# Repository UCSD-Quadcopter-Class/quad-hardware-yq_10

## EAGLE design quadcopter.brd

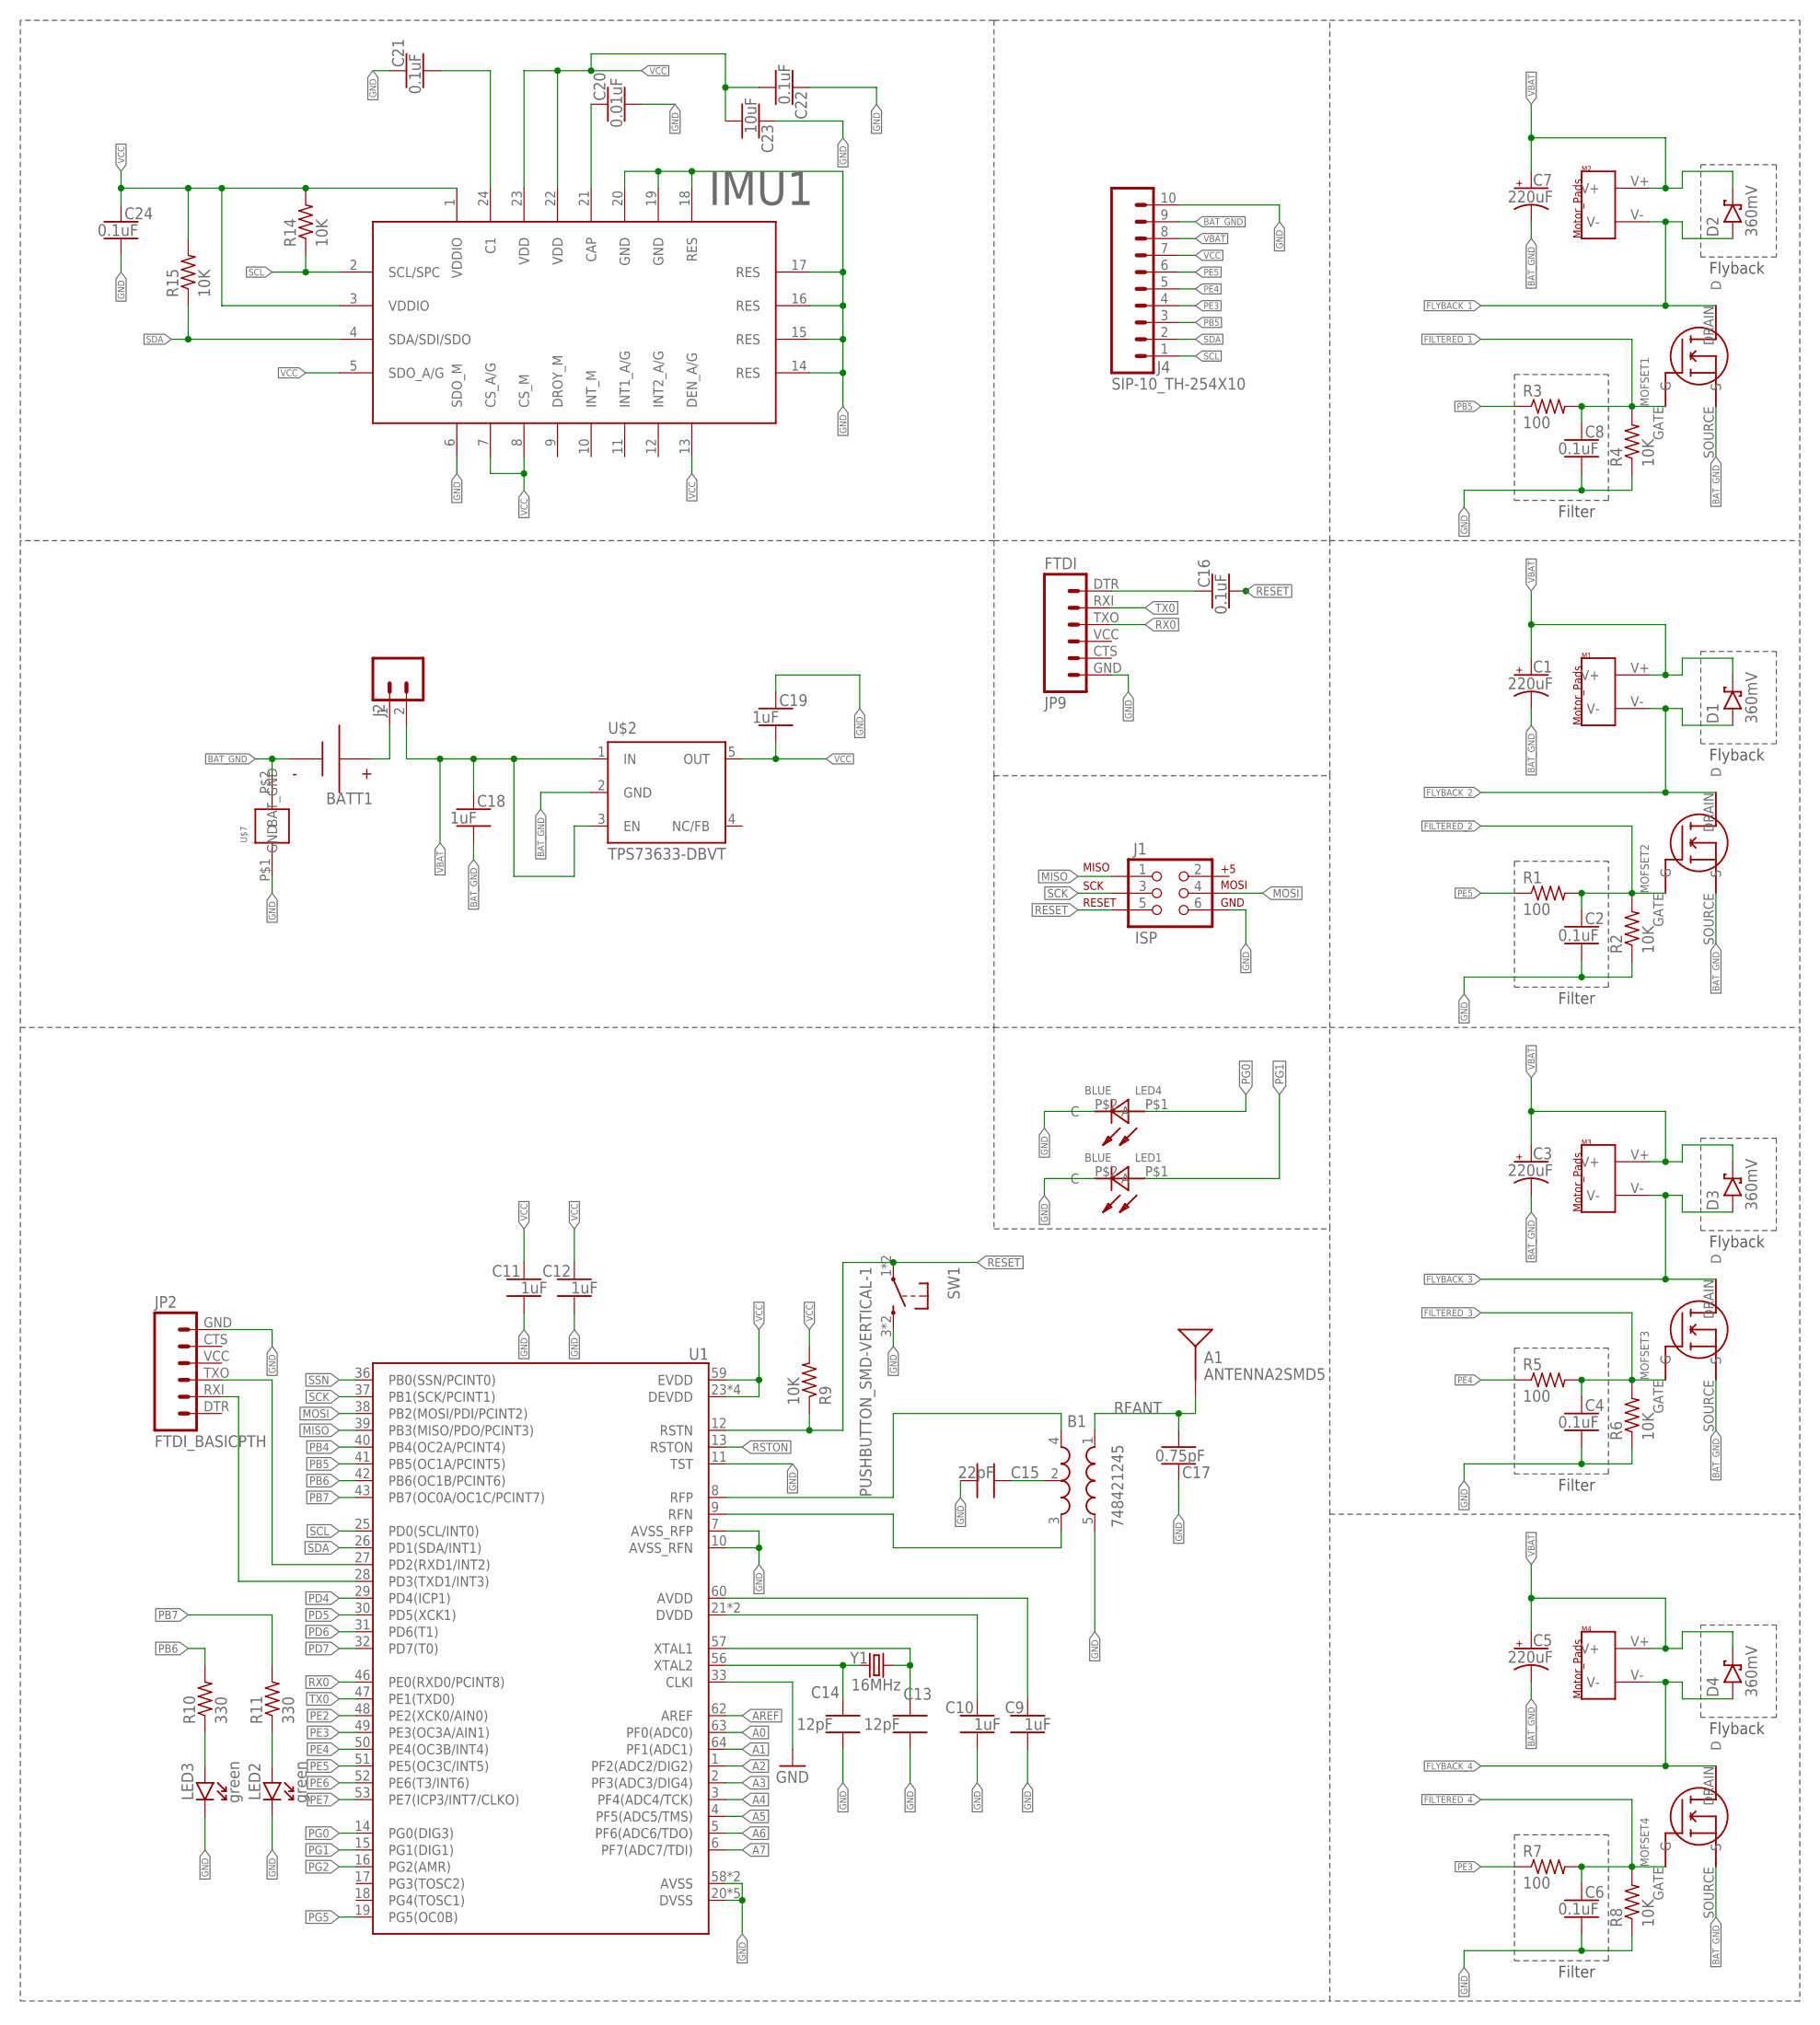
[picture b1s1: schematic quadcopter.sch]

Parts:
A1: ANTENNA2SMD5; ANTENNA-CHIP5
B1: 748421245; BALUN
BATT1: BATTERY-HUBSAN-W/HOLDER; BATTERY-W/HOLDER-380MAH-HUBSAN
C1, C3, C5, C7: 220uF; CAPMP7343X310_HS
C2, C4, C6, C8, C16, C21, C22, C24: 0.1uF; CAPC2012X140_HS
C9, C10, C11, C12, C18, C19: 1uF; CAPC2012X140_HS
C13, C14: 12pF; CAPC2012X140_HS
C15: 22pF; CAPC2012X140_HS
C17: 0.75pF; CAPC2012X140_HS
C20: 0.01uF; CAPC2012X140_HS
C23: 10uF; CAPC2012X140_HS
D1, D2, D3, D4: 360mV; SOD3716X135_HS
IMU1: 9_AXIS_IMU
J1: ISP; 2X3-NS
J2: MALE_HEADER_2POS-2X1-0.1IN; MALE_HEADER_2X1_0.1IN
J4: SIP-10_TH-254X10; HDRV10W63P254_10X1_2540X254H838_HS
JP2: FTDI_BASICPTH; FTDI_BASIC
JP9: FTDI; FTDI_BASIC
LED1, LED4: BLUE; CUT_TAPE
LED2, LED3: green; LEDSC125X200X120-2_HS
M1, M2, M3, M4: MOTOR_PADS
MOFSET1, MOFSET2, MOFSET3, MOFSET4: SI2302CDS_N_MOFSETSI2302CDS; N-CHANNEL_MOSFET
R1, R3, R5, R7: 100; RESC2012X60_HS
R2, R4, R6, R8, R9, R14, R15: 10K; RESC2012X60_HS
R10, R11: 330; RESC2012X60_HS
SW1: PUSHBUTTON_SMD-VERTICAL-1; TE_FSM8JSMA_HS
U1: ATMEGA128RFA1; QFN-64
U$2: TPS73633-DBVT; SOT23-DBV
U$7: NET_BRIDGE
Y1: 16MHz; CRYSTAL-SMD-5X3

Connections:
A0: U1.63 (PF0(ADC0))
A1: U1.64 (PF1(ADC1))
A2: U1.1 (PF2(ADC2/DIG2))
A3: U1.2 (PF3(ADC3/DIG4))
A4: U1.3 (PF4(ADC4/TCK))
A5: U1.4 (PF5(ADC5/TMS))
A6: U1.5 (PF6(ADC6/TDO))
A7: U1.6 (PF7(ADC7/TDI))
AREF: U1.62 (AREF)
AVDD: C9.1, U1.60 (AVDD)
BAT_GND: BATT1.- (N), C1.2 (-), C3.2 (-), C5.2 (-), C7.2 (-), C18.2, J4.9, MOFSET1.SOURCE (S), MOFSET2.SOURCE (S), MOFSET3.SOURCE (S), MOFSET4.SOURCE (S), U$2.2 (GND), U$7.P$2 (GND)
DTR: C16.1, JP9.DTR (1)
DVDD: C10.1, U1.21 (DVDD), U1.22 (DVDD)
FILTERED_1: C8.1, MOFSET1.GATE (G), R3.2, R4.2
FILTERED_2: C2.1, MOFSET2.GATE (G), R1.2, R2.2
FILTERED_3: C4.1, MOFSET3.GATE (G), R5.2, R6.2
FILTERED_4: C6.1, MOFSET4.GATE (G), R7.2, R8.2
FLYBACK_1: D2.A, M2.V-, MOFSET1.DRAIN (D)
FLYBACK_2: D1.A, M1.V-, MOFSET2.DRAIN (D)
FLYBACK_3: D3.A, M3.V-, MOFSET3.DRAIN (D)
FLYBACK_4: D4.A, M4.V-, MOFSET4.DRAIN (D)
GND: B1.5 (GND), C2.2, C4.2, C6.2, C8.2, C9.2, C10.2, C11.2, C12.2, C13.2, C14.2, C15.2, C17.1, C19.1, C20.2, C21.1, C22.1, C23.1, C24.2, IMU1.6 (SDO_M), IMU1.14 (RES), IMU1.15 (RES), IMU1.16 (RES), IMU1.17 (RES), IMU1.18 (RES), IMU1.19 (GND), IMU1.20 (GND), J1.6, J4.10, JP2.GND (6), JP9.GND (6), LED1.P$2 (C), LED2.C, LED3.C, LED4.P$2 (C), R2.1, R4.1, R6.1, R8.1, SW1.3 (2), SW1.4 (2), U1.7 (AVSS_RFP), U1.10 (AVSS_RFN), U1.11 (TST), U1.20 (DVSS), U1.24 (DVSS), U1.33 (CLKI), U1.35 (DVSS), U1.45 (DVSS), U1.55 (DVSS), U1.58 (AVSS), U1.61 (AVSS), U$7.P$1 (BAT_GND)
MISO: J1.1, U1.39 (PB3(MISO/PDO/PCINT3))
MOSI: J1.4, U1.38 (PB2(MOSI/PDI/PCINT2))
unnamed: C20.1, IMU1.21 (CAP)
unnamed: C21.2, IMU1.24 (C1)
unnamed: JP2.RXI (2), U1.28 (PD3(TXD1/INT3))
unnamed: JP2.TXO (3), U1.27 (PD2(RXD1/INT2))
unnamed: BATT1.+, J2.1
unnamed: C13.1, U1.57 (XTAL1), Y1.3 (2)
unnamed: C14.1, U1.56 (XTAL2), Y1.1
unnamed: B1.2 (GND), C15.1
unnamed: LED3.A, R10.1
unnamed: LED2.A, R11.1
unnamed: B1.4 (OUT1), U1.8 (RFP)
unnamed: B1.3 (OUT2), U1.9 (RFN)
PB4: U1.40 (PB4(OC2A/PCINT4))
PB5: J4.3, R3.1, U1.41 (PB5(OC1A/PCINT5))
PB6: R10.2, U1.42 (PB6(OC1B/PCINT6))
PB7: R11.2, U1.43 (PB7(OC0A/OC1C/PCINT7))
PD4: U1.29 (PD4(ICP1))
PD5: U1.30 (PD5(XCK1))
PD6: U1.31 (PD6(T1))
PD7: U1.32 (PD7(T0))
PE2: U1.48 (PE2(XCK0/AIN0))
PE3: J4.4, R7.1, U1.49 (PE3(OC3A/AIN1))
PE4: J4.5, R5.1, U1.50 (PE4(OC3B/INT4))
PE5: J4.6, R1.1, U1.51 (PE5(OC3C/INT5))
PE6: U1.52 (PE6(T3/INT6))
PE7: U1.53 (PE7(ICP3/INT7/CLKO))
PG0: LED4.P$1 (A), U1.14 (PG0(DIG3))
PG1: LED1.P$1 (A), U1.15 (PG1(DIG1))
PG2: U1.16 (PG2(AMR))
PG5: U1.19 (PG5(OC0B))
RESET: C16.2, J1.5, R9.1, SW1.1, SW1.2 (1), U1.12 (RSTN)
RFANT: A1.FEED, B1.1 (IN), C17.2
RSTON: U1.13 (RSTON)
RX0: JP9.TXO (3), U1.46 (PE0(RXD0/PCINT8))
SCK: J1.3, U1.37 (PB1(SCK/PCINT1))
SCL: IMU1.2 (SCL/SPC), J4.1, R14.1, U1.25 (PD0(SCL/INT0))
SDA: IMU1.4 (SDA/SDI/SDO), J4.2, R15.1, U1.26 (PD1(SDA/INT1))
SSN: U1.36 (PB0(SSN/PCINT0))
TX0: JP9.RXI (2), U1.47 (PE1(TXD0))
VBAT: C1.1 (+), C3.1 (+), C5.1 (+), C7.1 (+), C18.1, D1.C, D2.C, D3.C, D4.C, J2.2, J4.8, M1.V+, M2.V+, M3.V+, M4.V+, U$2.1 (IN), U$2.3 (EN)
VCC: C11.1, C12.1, C19.2, C22.2, C23.2, C24.1, IMU1.1 (VDDIO), IMU1.3 (VDDIO), IMU1.5 (SDO_A/G), IMU1.7 (CS_A/G), IMU1.8 (CS_M), IMU1.13 (DEN_A/G), IMU1.22 (VDD), IMU1.23 (VDD), J4.7, R9.2, R14.2, R15.2, U1.23 (DEVDD), U1.34 (DEVDD), U1.44 (DEVDD), U1.54 (DEVDD), U1.59 (EVDD), U$2.5 (OUT)

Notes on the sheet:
Filter
Flyback

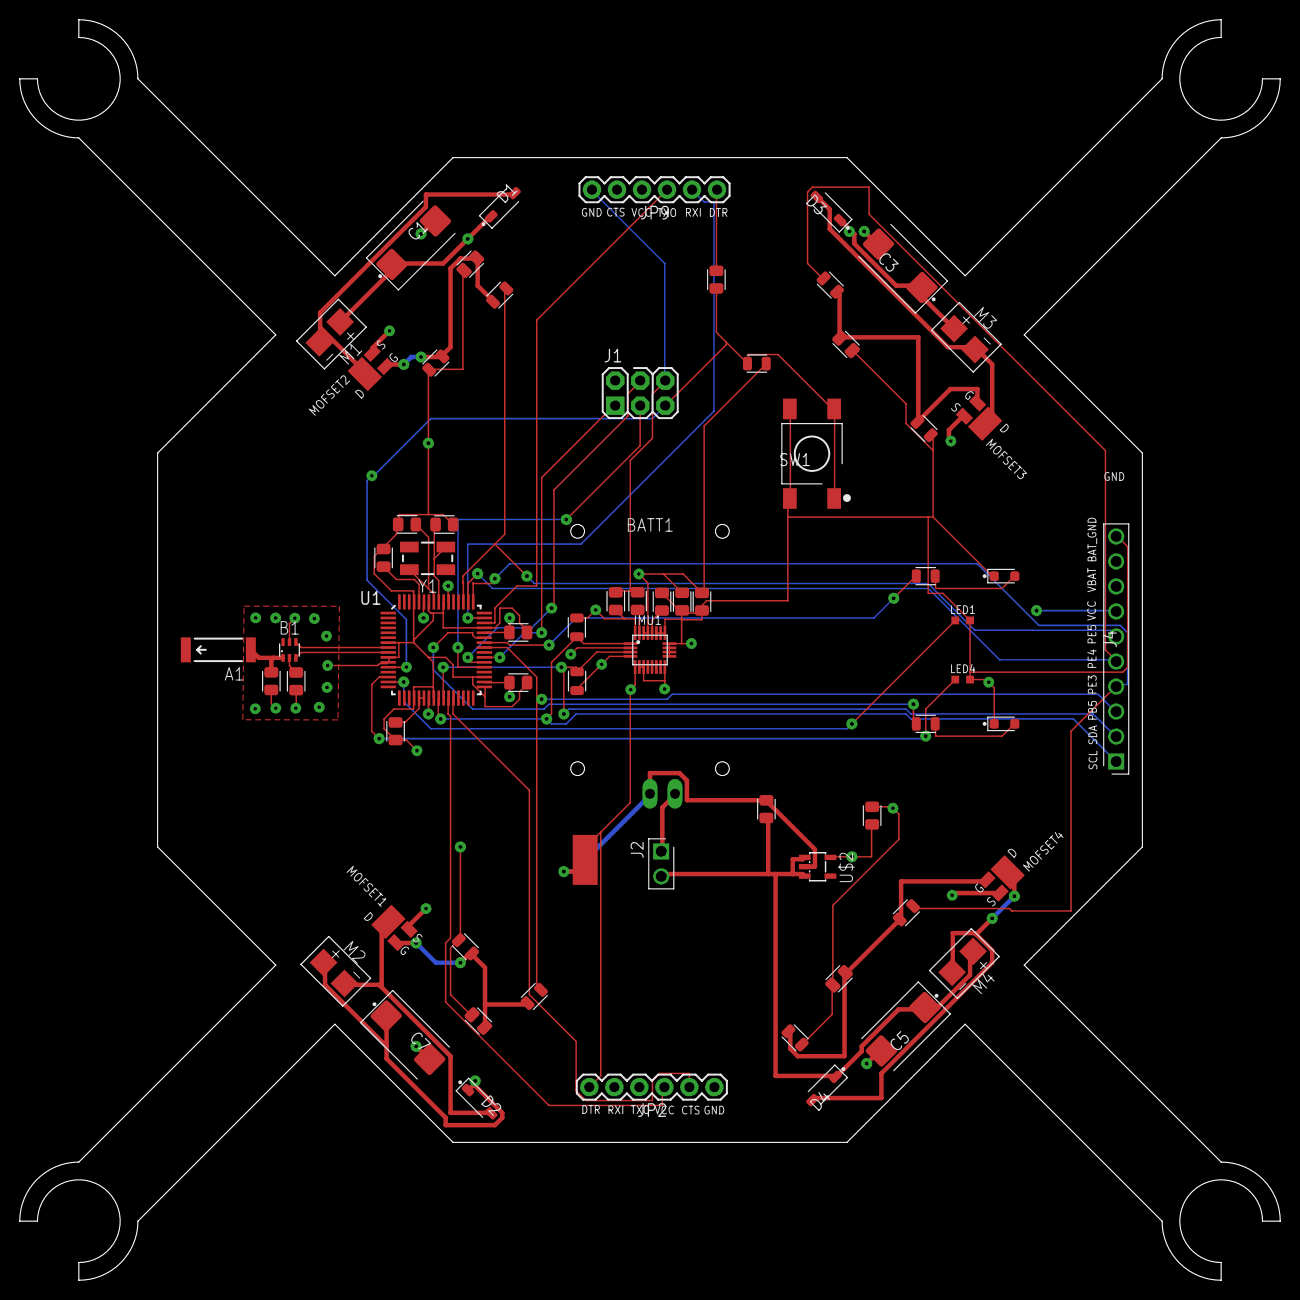
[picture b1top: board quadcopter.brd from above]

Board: 4 copper layers, 128.0 x 128.0 mm, 67 parts (0 on the bottom side), 44 nets.

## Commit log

2017-04-19 LED discrete indication datasheet
    The LED datasheet referred to draw the smd LED library.
2017-04-19 Student built library and LED library
    LED library is built based on the datasheet uploaded into the datasheet folder.
2017-04-20 initial-schematic
    Lab 4 Part A
2017-04-20 Modification to these two libraries
    Added net bridge into the prebuilt one and added few new capacitors and resistors with different values
2017-04-20 led_notes.txt
    Describe how the LED was selected and designed.
2017-04-25 Question about schematic design by Group 9
2017-04-25 Question about our design found by Group 9
2017-04-25 Schematic edited on April 24th
2017-04-25 Edited IMU and MOSFET pad size
2017-04-25 Modified library of Yueqi and new lbr from Yupei
2017-04-27 instructior review of original schematic
2017-05-02 Modified schematic and initial board
    Schematic has been modified based on design review and board has been layout.
2017-05-04 Board review by Group 9
2017-05-04 Review of group 9 by group 10
2017-05-08 Libraries pass eagle lint
    Reviewers are done.
2017-05-08 Version before generating cam
2017-05-08 DRU
    DRU used for check
2017-05-09 Version May 8th 11pm
    Version before rerun the autorouter with new dru
2017-05-09 Board and Schematic that pass DFM
2017-05-09 Board passed DFM
2017-05-09 Schematic passed DFM
2017-05-09 Create CAM
2017-05-09 Create A
2017-05-09 Create create CAM directory
2017-05-09 CAM files for our design
2017-05-09 Zip file for CAM files
2017-05-09 DRU used
2017-05-10 Board design review 1
2017-05-11 New board passed DFM using new DRU and CAM
2017-05-11 New board passed DFM with new DRU and CAM
2017-05-11 new schematic passed DFM
2017-05-11 CAM files passed DFM with new DRU and CAM on 5/10
2017-05-11 new CAM files
2017-05-11 new schematic May 10th
2017-05-11 NEW dru file
2017-05-11 NEW CAM
2017-05-11 New CAM files after Prof. review on May 10th
2017-05-11 New board after Prof. review on May 10th
2017-05-11 New schematic after Prof. review on May 10th
2017-05-11 How I fixed the problems in the review on May 10th
2017-05-11 Modified the pad size of MOSFET
2017-05-11 new CAM files after Prof.'s review on May 10th
2017-05-11 new board after Prof.'s review on May 10th
2017-05-11 new schematic after Prof.'s review on May 10th
2017-05-11 Updated review
2017-05-11 New board with de cap connecting to microcon
2017-05-11 New CAM file after modifying decoup cap
2017-05-11 new cam layer files after modifying decoup cap
2017-05-11 New schematic after modifying decoup cap
2017-05-12 New cam files modified decoupling cap for imu
2017-05-12 new board modified decoupling cap for imu
2017-05-12 cam layer files modified decoupling cap for imu
2017-05-14 more schematic comments from swanson
2017-05-14 New cam file fixed decoupling caps in motor driver
2017-05-14 New cam files fixed problems about decoupling mtrs
2017-05-14 New schematic fixed decoupling caps
2017-05-14 New board fixed de cap and bat_gnd
2017-05-15 Replaced decoupling caps for motor drivers
